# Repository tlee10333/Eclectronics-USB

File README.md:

# Eclectronics Spring 2026 Final Project - Wireless USB Communication Board 
## By: Allan Huang, Trinity Lee, Venkadesh Eswaranandam

This repository contains documentation for a wireless USB communication board. 
TBD

# Documentation
Below are links to documentation provided by the official manufacturers and were used as reference for this project in schematic design and layout. 

## Nordic Semiconductor nRF5340 
[General Documentation Website](https://docs.nordicsemi.com/category/nrf5340-category)

[Download link to Product Specification PDF/Datasheet v1.6](https://docs-be.nordicsemi.com/bundle/ps_nrf5340/page/nRF5340_PS_v1.6.pdf?_LANG=enus) 

## Nordic Semiconductor nRF7002 
[General Documentation Website](https://docs.nordicsemi.com/category/nrf7002-category)

[Download link to Product Specification PDF/Datasheet v1.2](https://docs-be.nordicsemi.com/bundle/ps_nrf7002/attach/nRF7002_PS_v1.2.pdf?_LANG=enus)

## TS3USB30E Mux

[General Documentation Website](https://www.ti.com/product/TS3USB30E?utm_source=google&utm_medium=cpc&utm_campaign=asc-null-null-GPN_EN-cpc-pf-google-ww_en_cons&utm_content=TS3USB30E&ds_k=TS3USB30E&DCM=yes&gclsrc=aw.ds&gad_source=1&gad_campaignid=14388345080&gbraid=0AAAAAC068F08dQr31V7reTsWFYpttdheS&gclid=Cj0KCQjwqPLOBhCiARIsAKRMPZrFZs5P4qY13GjpmxYn9nQQtVWeXslW-kTBu4hEDNIcvVn2RVSppWgaAsXEEALw_wcB)

[Link to Product Specification PDF/Datasheet](https://www.ti.com/lit/ds/symlink/ts3usb30e.pdf?ts=1776081731034&ref_url=https%253A%252F%252Fwww.ti.com%252Fproduct%252FTS3USB30E)

## TBD
[General Documentation Website]()

[Download link to Product Specification PDF/Datasheet]()

# References
Below are links that were used for references (cthis section can be deleted if we want to)

[nRF7002 DK datasheet](https://docs-be.nordicsemi.com/bundle/ug_nrf7002_dk/attach/nRF7002_DK_User_Guide_v1.0.0.pdf?_LANG=enus)

[nRF5340 DK datasheet](https://docs-be.nordicsemi.com/bundle/ug_nrf5340_dk/attach/nRF5340_DK_User_Guide_v2.0.2.pdf?_LANG=enus)

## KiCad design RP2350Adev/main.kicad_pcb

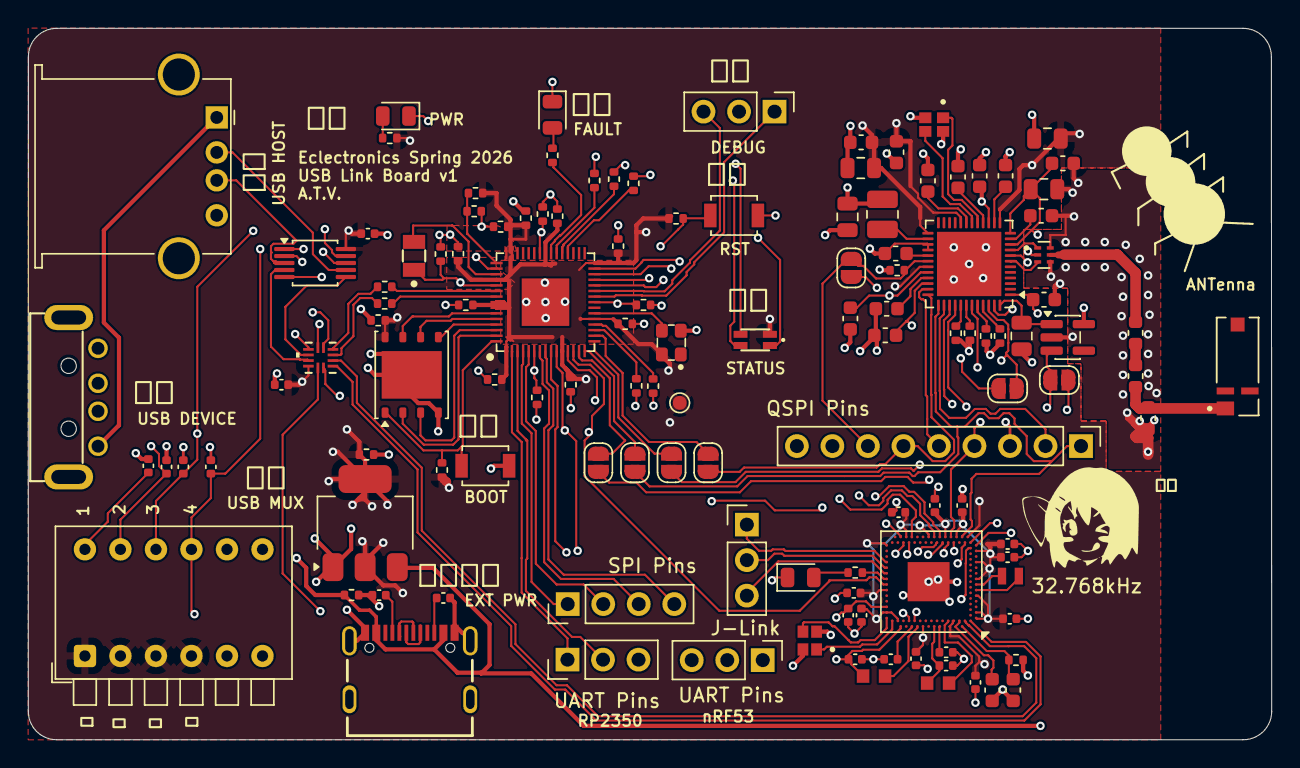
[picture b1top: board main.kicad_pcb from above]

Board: 4 copper layers, 88.9 x 50.9 mm, 124 parts (0 on the bottom side), 111 nets.

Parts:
A301: NN03-320; XCVR_NN03-320
C201, C202: 4.7µF; C_0603_1608Metric
C203, C206, C207, C208, C209: 1.0µF; C_0402_1005Metric
C204, C210, C211, C212, C213, C214, C215, C216, C217: 100nF; C_0402_1005Metric
C205: 2.2nF; C_0402_1005Metric
C301, C314: 0.47uF; C_0603_1608Metric
C302, C303: 100nF; C_0603_1608Metric
C304, C305, C315, C316: 4.7uF; C_0805_2012Metric
C306: 2.2uF; C_0805_2012Metric
C307: 22nF; C_0603_1608Metric
C308: 0.22uF; C_0603_1608Metric
C309, C318: 2.2uF; C_0603_1608Metric
C310, C311, C312, C313: 1uF; C_0603_1608Metric
C317: 10nF; C_0603_1608Metric
C401, C403: 10µF; R_0402_1005Metric
C402, C406, C407, C408, C409, C410, C411, C412, C415, C417: 0.1µF; R_0402_1005Metric
C404, C405, C413, C414, C416: 4.7µF; R_0402_1005Metric
C701, C702: 1uF; C_0402_1005Metric
D201, D402: LED; LED_0805_2012Metric
D401: PWR; LED_0805_2012Metric
D403: IN-S85TATRGB
J201: J-Link; PinHeader_1x03_P2.54mm_Vertical
J202: SPI Pins; PinHeader_1x04_P2.54mm_Vertical
J203: QSPI Pins; PinHeader_1x09_P2.54mm_Vertical
J204: UART Pins; PinHeader_1x03_P2.54mm_Vertical
J401: UART; PinHeader_1x03_P2.54mm_Vertical
J402: DEBUG; PinHeader_1x03_P2.54mm_Vertical
J701: USB_A_Male; USB_A_0480370001
J702: USB_A_Female; USB_A_Stewart_SS-52100-001_Horizontal
J703: USB4105-GF-A
JP101, JP102, JP103, JP104, JP105, JP106, JP107: SolderJumper_2_Open; SolderJumper-2_P1.3mm_Open_RoundedPad1.0x1.5mm
L201: 10uH; INDC1608X95N
L202: 10µH; INDC1608X95N
L301: 7.5nH; L_0603_1608Metric
L302, L303: 2.7nH; L_0603_1608Metric
L304: 3.3uH; L_1008_2520Metric
L401: 3.3µH; AOTA-B201610S3R3-101-T
M701: TS3USB3031RMGR; RMG12_TEX
R101, R102, R404, R405: 27Ω; R_0402_1005Metric
R201: 2.2 Ω; R_0402_1005Metric
R202, R403, R407, R409, R410: 1K; R_0402_1005Metric
R301, R302, R303, R304, R305: 100k; R_0402_1005Metric
R401, R402, R408: 5.1K; R_0402_1005Metric
R406: 33Ω; R_0402_1005Metric
R701, R702, R703, R704: 10K; C_0402_1005Metric
R705, R706: 5.1K; C_0402_1005Metric
S401: RST; SW_SPST_B3U-1000P
S402: BOOT; SW_SPST_B3U-1000P
SW701: SW_DIP_x06; SW_DIP_SPSTx06_Piano_10.8x16.8mm_W7.62mm_P2.54mm
TP101: TestPoint; TestPoint_Pad_D1.0mm
U201: nRF5340-QKxx; Nordic_AQFN-94-1EP_7x7mm_P0.4mm
U301: TCK106AF; SC-74A-5_1.55x2.9mm_P0.95mm
U302: LFD_Diplexer; FIL_LFD182G45DCJD247
U303: nRF7002-QFAA; QFN-48-1EP_6x6mm_P0.4mm_EP4.6x4.6mm
U401: LD1117S33TR_SOT223; SOT-223-3_TabPin2
U402: W25Q32JV; WSON-8-1EP_6x5mm_P1.27mm_EP3.4x4.3mm
U403: RP2350A; RP2350A_QFN-60_EP_7.75x7.75_Pitch0.4mm
U701: TS3USB30EDGSR; VSSOP-10_3x3mm_P0.5mm
X201: 32MHz; XTAL_ABM11W-32.0000MHZ-8-D1X-T3
X202: 32.768kHz; XTAL_CM9V-T1A-32.768KHZ-9PF-20PPM-TA-QC
X301: XTAL-40; XTAL_ABM11W-32.0000MHZ-8-D1X-T3
X401: IQXO-791

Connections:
+1V1: C405.2, C415.2, C416.2, C417.2, L401.1, U403.6 (DVDD), U403.23 (DVDD), U403.39 (DVDD), U403.50 (VREG_FB)
+3V3: C208.2, C209.2, C210.2, C211.2, C212.2, C213.2, C214.2, C215.2, C216.2, C217.2, C305.1, C311.1, C315.1, C318.1, C402.2, C403.1, C404.2, C406.2, C407.2, C408.2, C409.2, C410.2, C411.2, C412.2, C413.2, C701.2, C702.2, D403.3, M701.12 (VCC), R401.1, R402.1, R403.1, R406.2, SW701.1, SW701.2, SW701.3, SW701.4, TP101.1, U201.A19 (VDD), U201.AC1 (VDD), U201.AG1 (VDD), U201.AJ31 (VDD), U201.AL3 (VDD), U201.AL7 (VDD), U201.AL11 (VDD), U201.AL17 (VDD), U201.AL25 (VDD), U201.B8 (VDD), U201.B28 (VDD), U201.C1 (VDD), U201.E1 (VDDH), U201.E31 (VDD), U201.L1 (VDD), U201.N31 (VDD), U201.U1 (VDD), U301.5 (VIN), U303.13 (VBAT), U303.20 (AFEVBAT), U303.25 (BUCKVBAT), U303.31 (BUCKVBATS), U401.2 (VO), U402.8 (VDD), U403.1 (IOVDD), U403.11 (IOVDD), U403.20 (IOVDD), U403.30 (IOVDD), U403.38 (IOVDD), U403.44 (ADC_AVDD), U403.45 (IOVDD), U403.49 (VREG_VIN), U403.53 (USB_OTP_VDD), U403.54 (QSPI_IOVDD), U701.10 (VCC), X401.4 (VS)
+5V: C401.2, J701.1 (VBUS), J702.1 (VBUS), J703.A4B9 (VBUS), J703.B4A9 (VBUS), R201.1, U401.3 (VI)
/RP2350Adev/BOOT: R402.2, S402.2, U402.1 (~CS), U403.60 (~QSPI_CS)
/RP2350Adev/BUCK_EN: JP101.1 (A), U403.28 (GPIO17)
/RP2350Adev/D1+: M701.5 (USB2+), R405.1
/RP2350Adev/D1-: M701.6 (USB2-), R404.1
/RP2350Adev/D2+: R101.2, U403.18 (GPIO14)
/RP2350Adev/D2-: R102.2, U403.19 (GPIO15)
/RP2350Adev/GPIO22: R407.1, U403.34 (GPIO22)
/RP2350Adev/GPIO23: R408.1, U403.35 (GPIO23)
/RP2350Adev/GPIO24: R409.1, U403.36 (GPIO24)
/RP2350Adev/GPIO25: R410.1, U403.37 (GPIO25)
/RP2350Adev/HOST_IRQ: JP102.1 (A), U403.27 (GPIO16)
/RP2350Adev/IOVDD_EN: JP107.2 (B), U403.29 (GPIO18)
/RP2350Adev/MUX1_S0: M701.1 (SEL0), R701.1, SW701.12, U201.R31 (P1.10), U403.13 (GPIO9)
/RP2350Adev/MUX1_S1: M701.2 (SEL1), R702.1, SW701.11, U201.AK26 (P1.09), U403.12 (GPIO8)
/RP2350Adev/MUX2_OE: R703.1, SW701.10, U201.AL23 (P1.08), U403.10 (GPIO7), U701.9 (~OE)
/RP2350Adev/MUX2_S: R704.1, SW701.9, U201.AK24 (P1.07), U403.9 (GPIO6), U701.1 (S)
/RP2350Adev/RUN: R401.2, S401.2, U403.26 (RUN)
/RP2350Adev/SPI_CLK: J202.1, U201.AH2 (SCK/TRACEDATA3/P0.08), U403.4 (GPIO2)
/RP2350Adev/SPI_CLK2: JP106.1 (A), U403.14 (GPIO10)
/RP2350Adev/SPI_MISO: J202.3, U201.AK2 (MISO/TRACEDATA1/P0.10), U403.7 (GPIO4)
/RP2350Adev/SPI_MISO2: JP104.1 (A), U403.16 (GPIO12)
/RP2350Adev/SPI_MOSI: J202.2, U201.AJ1 (MOSI/TRACEDATA2/P0.09), U403.5 (GPIO3)
/RP2350Adev/SPI_MOSI2: JP103.1 (A), U403.15 (GPIO11)
/RP2350Adev/SPI_SS: J202.4, U201.AK4 (CSN/TRACEDATA0/P0.11), U403.8 (GPIO5)
/RP2350Adev/SPI_SS2: JP105.1 (A), U403.17 (GPIO13)
/RP2350Adev/SWCLK: J402.1, U403.24 (SWCLK)
/RP2350Adev/SWDIO: J402.3, U403.25 (SWDIO)
/USB_Mux_Periph/D1+: M701.3 (USB1+), U201.B2 (D+)
/USB_Mux_Periph/D1-: M701.4 (USB1-), U201.B4 (D-)
/USB_Mux_Periph/D3+: M701.7 (MHL+), R101.1
/USB_Mux_Periph/D3-: M701.8 (MHL-), R102.1
/nRF5340/BUCKEN: J203.7, JP101.2 (B), R301.1, U201.AL13 (P0.19), U303.30 (BUCKEN)
/nRF5340/COEX: J203.8, U303.43 (COEX_GRANT)
/nRF5340/HOST_IRQ: J203.9, JP102.2 (B), U201.AL15 (P0.21), U303.46 (HOST_IRQ)
/nRF5340/IOVDD_EN: JP107.1 (A), U201.AL27 (P0.24), U301.3 (CTRL)
/nRF5340/QSPI0: J203.1, JP103.2 (B), U201.AL5 (IO0/P0.13), U303.37 (QSPI_DATA0)
/nRF5340/QSPI1: J203.2, JP104.2 (B), U201.AK8 (IO1/P0.14), U303.38 (QSPI_DATA1)
/nRF5340/QSPI2: J203.3, U201.AK10 (IO2/P0.15), U303.39 (QSPI_DATA2)
/nRF5340/QSPI3: J203.4, U201.AL9 (IO3/P0.16), U303.40 (QSPI_DATA3)
/nRF5340/QSPI_CLK: J203.5, JP106.2 (B), U201.AK12 (SCK/P0.17), U303.35 (QSPI_CLK)
/nRF5340/QSPI_SS: J203.6, JP105.2 (B), U201.AK14 (CSN/P0.18), U303.36 (QSPI_SS)
/nRF5340/RX: J204.2, U201.B24 (P0.30)
/nRF5340/TX: J204.1, U201.B22 (P0.31)
/nRF7002/PWR_IOVDD: C303.1, C312.1, U303.1 (OTPVDD), U303.34 (PWRIOVDD)
/nRF7002/VDD_BUCK: C308.1, C314.1, C316.1, L304.2, U303.15 (RFBUCKVDD), U303.32 (PWRBUCKVDD)
GND: C201.2, C202.2, C203.2, C204.2, C205.2, C206.2, C207.2, C208.1, C209.1, C210.1, C211.1, C212.1, C213.1, C214.1, C215.1, C216.1, C217.1, C301.2, C302.2, C303.2, C304.2, C305.2, C306.2, C307.2, C308.2, C309.2, C310.2, C311.2, C312.2, C313.2, C314.2, C315.2, C316.2, C317.2, C318.2, C401.1, C402.1, C403.2, C404.1, C405.1, C406.1, C407.1, C408.1, C409.1, C410.1, C411.1, C412.1, C413.1, C414.1, C415.1, C416.1, C417.1, C701.1, C702.1, D201.1 (K), D401.1 (K), D402.1 (K), J204.3, J401.3, J402.2, J701.4 (GND), J701.5 (Shield), J702.4 (GND), J702.5 (Shield), J703.A1B12 (GND), J703.B1A12 (GND), J703.S1 (SHELL), J703.S2 (SHELL), J703.S3 (SHELL), J703.S4 (SHELL), L301.2, M701.9 (GND), R301.2, R302.2, R303.2, R304.2, R305.2, R701.2, R702.2, R703.2, R704.2, R705.2, R706.2, S401.1, S402.1, U201.EP (VSS), U301.2 (GND), U302.2 (GND), U302.5 (GND), U302.7 (GND), U303.27 (BUCKVSS), U303.28 (BUCKVSS), U303.47 (VSS), U303.49 (VSS), U401.1 (GND), U402.4 (GND), U402.9 (EP), U403.47 (VREG_PGND), U403.61 (GND), U701.5 (GND), X201.2 (G), X201.4 (G), X301.2 (G), X301.4 (G), X401.2 (GND)
unnamed: A301.1 (A), L301.1, L302.1
unnamed: D201.2 (A), R202.2
unnamed: D401.2 (A), R403.2
unnamed: D402.2 (A), R410.2
unnamed: D403.1, R407.2
unnamed: D403.2, R408.2
unnamed: D403.4, R409.2
unnamed: J201.1, U201.AC31 (~RESET)
unnamed: J201.2, U201.AA31 (SWDIO)
unnamed: J201.3, U201.W31 (SWDCLK)
unnamed: J401.1, U403.2 (GPIO0)
unnamed: J401.2, U403.3 (GPIO1)
unnamed: J701.3 (D+), U701.2 (D1+)
unnamed: J701.2 (D-), U701.8 (D1-)
unnamed: J702.3 (D+), U701.3 (D2+)
unnamed: J702.2 (D-), U701.7 (D2-)
unnamed: J703.A5 (CC1), R706.1
unnamed: J703.B5 (CC2), R705.1
unnamed: L302.2, L303.1
unnamed: M701.11 (D+), U701.4 (D+)
unnamed: M701.10 (D-), U701.6 (D-)
unnamed: L201.1, U201.A21 (DCC)
unnamed: L202.1, U201.B10 (DCCD)
unnamed: C207.1, U201.A13 (DECA)
unnamed: C206.1, L202.2, U201.A15 (DECD)
unnamed: C204.1, U201.A23 (DECN)
unnamed: C203.1, C205.1, L201.2, U201.A27 (DECR), U201.G31 (DECRF)
unnamed: C202.1, U201.B6 (DECUSB)
unnamed: R202.1, U201.U31 (P0.29)
unnamed: C201.1, R201.2, U201.A5 (VBUS)
unnamed: U201.C31 (XC1), X201.3
unnamed: U201.B30 (XC2), X201.1
unnamed: U201.N1 (XL1/P0.00), X202.1
unnamed: U201.R1 (XL2/P0.01), X202.2
unnamed: C306.1, U301.1 (VOUT), U303.48 (IOVDD)
unnamed: U302.1 (2.4G), U303.9 (TXRF0)
unnamed: U302.3 (5G), U303.7 (TXRF1)
unnamed: L303.2, U302.6 (COM)
unnamed: C310.1, U303.19 (AFELDO)
unnamed: L304.1, U303.26 (BUCKOUT)
unnamed: C317.1, U303.29 (BUCKVMID)
unnamed: R303.1, U303.42 (COEX_REQ)
unnamed: R302.1, U303.41 (COEX_STATUS0)
unnamed: C313.1, U303.33 (DIGVDD)
unnamed: C302.1, C304.1, U303.8 (PAVDD1), U303.10 (PAVDD0), U303.12 (PALDO)
unnamed: C307.1, U303.14 (RFVDD)
unnamed: R304.1, U303.44 (SW_CTRL0)
unnamed: R305.1, U303.45 (SW_CTRL1)
unnamed: C301.1, U303.11 (SXLDO)
unnamed: C309.1, U303.16 (XOLDO)
unnamed: U303.18 (XON), X301.3
unnamed: U303.17 (XOP), X301.1
unnamed: U402.5 (DI/IO0), U403.57 (QSPI_SD0)
unnamed: U402.2 (DO/IO1), U403.59 (QSPI_SD1)
unnamed: U402.6 (SCK), U403.56 (QSPI_SCLK)
unnamed: U402.7 (~HOLD/IO3), U403.55 (QSPI_SD3)
unnamed: U402.3 (~WP/IO2), U403.58 (QSPI_SD2)
unnamed: R405.2, U403.52 (USB_D+)
unnamed: R404.2, U403.51 (USB_D-)
unnamed: C414.2, R406.1, U403.46 (VREG_AVDD)
unnamed: L401.2, U403.48 (VREG_LX)
unnamed: U403.21 (XIN), X401.3 (OUT)

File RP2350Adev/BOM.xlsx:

Id | Designator | Footprint | Quantity | Designation | Supplier and ref
1 | R405,R102,R101,R404 | R_0402_1005Metric | 4 | 27Ω
2 | R702,R701,R703,R704 | C_0402_1005Metric | 4 | 10K
3 | C407,C402,C417,C409,C410,C412,C408,C415,C411,C406 | R_0402_1005Metric | 10 | 0.1µF
4 | C201,C202 | C_0603_1608Metric | 2 | 4.7µF
5 | U201 | Nordic_AQFN-94-1EP_7x7mm_P0.4mm | 1 | nRF5340-QKxx
6 | D402,D201 | LED_0805_2012Metric | 2 | LED
7 | R201 | R_0402_1005Metric | 1 | 2.2 Ω
8 | U401 | SOT-223-3_TabPin2 | 1 | LD1117S33TR_SOT223
9 | C302,C303 | C_0603_1608Metric | 2 | 100nF
10 | C212,C214,C204,C215,C210,C213,C216,C211,C217 | C_0402_1005Metric | 9 | 100nF
11 | C308 | C_0603_1608Metric | 1 | 0.22uF
12 | C208,C203,C206,C207,C209 | C_0402_1005Metric | 5 | 1.0µF
13 | R705,R706 | C_0402_1005Metric | 2 | 5.1K
14 | D401 | LED_0805_2012Metric | 1 | PWR
15 | A301 | XCVR_NN03-320 | 1 | NN03-320
16 | J204 | PinHeader_1x03_P2.54mm_Vertical | 1 | UART Pins
17 | R406 | R_0402_1005Metric | 1 | 33Ω
18 | R401,R402,R408 | R_0402_1005Metric | 3 | 5.1K
19 | R410,R409,R202,R403,R407 | R_0402_1005Metric | 5 | 1K
20 | C314,C301 | C_0603_1608Metric | 2 | 0.47uF
21 | C306 | C_0805_2012Metric | 1 | 2.2uF
22 | R305,R302,R301,R303,R304 | R_0402_1005Metric | 5 | 100k
23 | J201 | PinHeader_1x03_P2.54mm_Vertical | 1 | J-Link
24 | L301 | L_0603_1608Metric | 1 | 7.5nH
25 | TP101 | TestPoint_Pad_D1.0mm | 1 | TestPoint
26 | C401,C403 | R_0402_1005Metric | 2 | 10µF
27 | C304,C316,C305,C315 | C_0805_2012Metric | 4 | 4.7uF
28 | C405,C414,C404,C416,C413 | R_0402_1005Metric | 5 | 4.7µF
29 | C307 | C_0603_1608Metric | 1 | 22nF
30 | C313,C310,C312,C311 | C_0603_1608Metric | 4 | 1uF
31 | X301 | XTAL_ABM11W-32.0000MHZ-8-D1X-T3 | 1 | XTAL-40
32 | C317 | C_0603_1608Metric | 1 | 10nF
33 | S401 | SW_SPST_B3U-1000P | 1 | RST
34 | J402 | PinHeader_1x03_P2.54mm_Vertical | 1 | DEBUG
35 | J203 | PinHeader_1x09_P2.54mm_Vertical | 1 | QSPI Pins
36 | U701 | VSSOP-10_3x3mm_P0.5mm | 1 | TS3USB30EDGSR
37 | L202 | INDC1608X95N | 1 | 10µH
38 | J401 | PinHeader_1x03_P2.54mm_Vertical | 1 | UART
39 | X202 | XTAL_CM9V-T1A-32.768KHZ-9PF-20PPM-TA-QC | 1 | 32.768kHz
40 | C309,C318 | C_0603_1608Metric | 2 | 2.2uF
41 | U301 | SC-74A-5_1.55x2.9mm_P0.95mm | 1 | TCK106AF
42 | L201 | INDC1608X95N | 1 | 10uH
43 | U403 | RP2350A_QFN-60_EP_7.75x7.75_Pitch0.4mm | 1 | RP2350A
44 | J702 | USB_A_Stewart_SS-52100-001_Horizontal | 1 | USB_A_Female
45 | S402 | SW_SPST_B3U-1000P | 1 | BOOT
46 | C702,C701 | C_0402_1005Metric | 2 | 1uF
47 | SW701 | SW_DIP_SPSTx06_Piano_10.8x16.8mm_W7.62mm_P2.54mm | 1 | SW_DIP_x06
48 | L304 | L_1008_2520Metric | 1 | 3.3uH
49 | X401 | IQXO-791 | 1 | IQXO-791
50 | L302,L303 | L_0603_1608Metric | 2 | 2.7nH
51 | U302 | FIL_LFD182G45DCJD247 | 1 | LFD_Diplexer
52 | J202 | PinHeader_1x04_P2.54mm_Vertical | 1 | SPI Pins
53 | U303 | QFN-48-1EP_6x6mm_P0.4mm_EP4.6x4.6mm | 1 | nRF7002-QFAA
54 | M701 | RMG12_TEX | 1 | TS3USB3031RMGR
55 | C205 | C_0402_1005Metric | 1 | 2.2nF
56 | X201 | XTAL_ABM11W-32.0000MHZ-8-D1X-T3 | 1 | 32MHz
57 | U402 | WSON-8-1EP_6x5mm_P1.27mm_EP3.4x4.3mm | 1 | W25Q32JV
58 | J703 | USB4105-GF-A | 1 | USB4105-GF-A
59 | J701 | USB_A_0480370001 | 1 | USB_A_Male
60 | D403 | IN-S85TATRGB | 1 | IN-S85TATRGB
61 | L401 | AOTA-B201610S3R3-101-T | 1 | 3.3µH

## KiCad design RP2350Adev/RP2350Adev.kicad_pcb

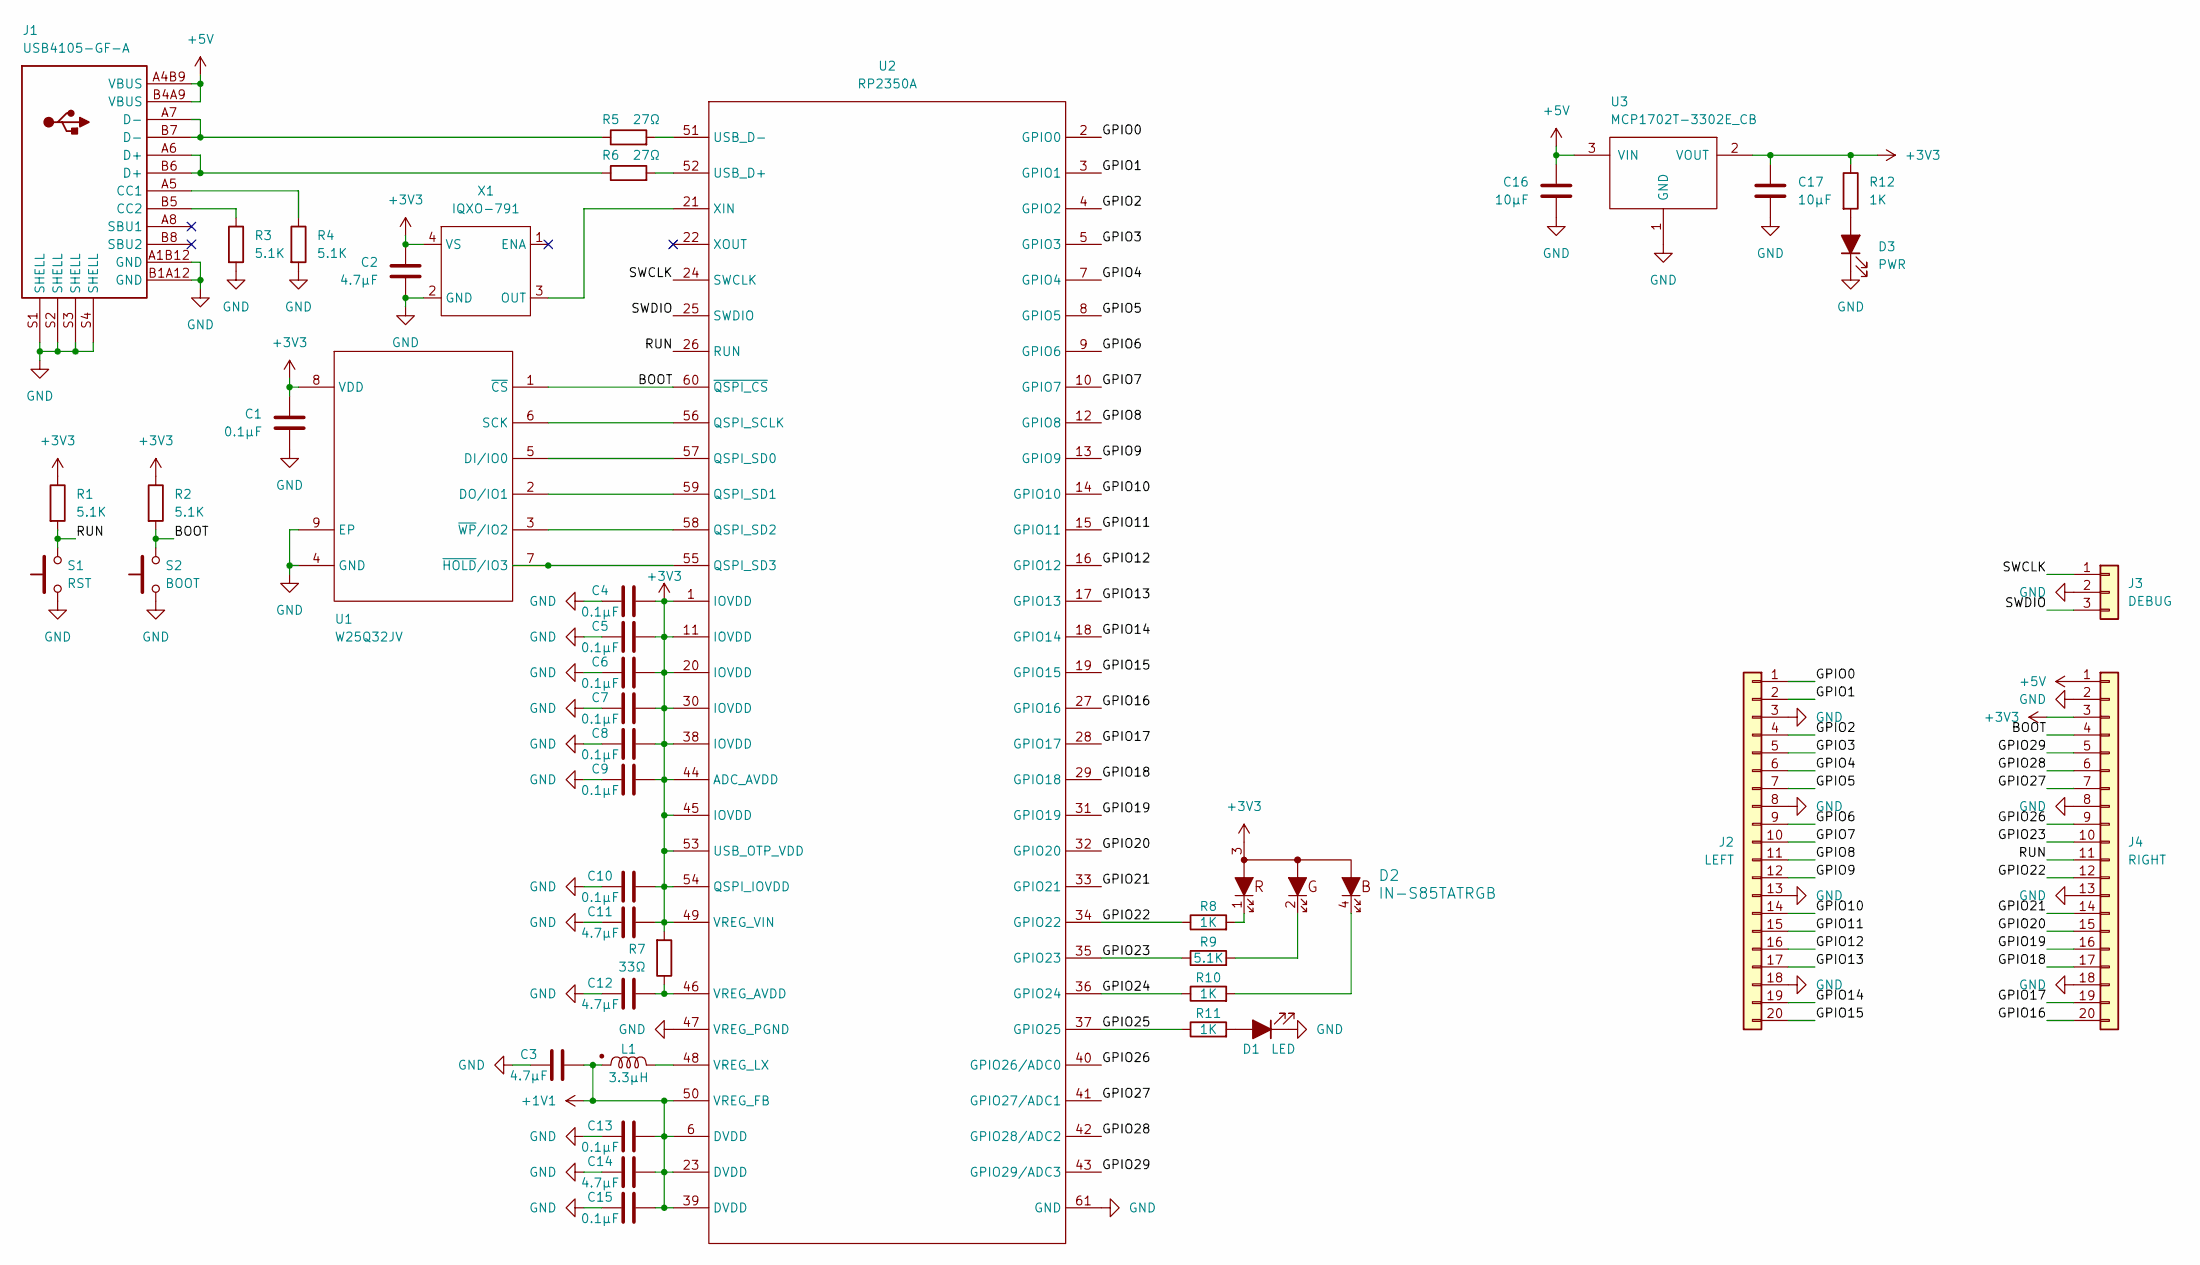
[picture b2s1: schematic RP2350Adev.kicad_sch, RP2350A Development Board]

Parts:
C1, C4, C5, C6, C7, C8, C9, C10, C13, C15: 0.1µF; R_0402_1005Metric
C2, C3, C11, C12, C14: 4.7µF; R_0402_1005Metric
C16, C17: 10µF; R_0402_1005Metric
D1: LED; LED_0805_2012Metric
D2: IN-S85TATRGB
D3: PWR; LED_0805_2012Metric
J1: USB4105-GF-A
J2: LEFT; PinHeader_1x20_P2.54mm_Vertical
J3: DEBUG; PinHeader_1x03_P1.00mm_Vertical
J4: RIGHT; PinHeader_1x20_P2.54mm_Vertical
L1: 3.3µH; AOTA-B201610S3R3-101-T
R1, R2, R3, R4, R9: 5.1K; R_0402_1005Metric
R5, R6: 27Ω; R_0402_1005Metric
R7: 33Ω; R_0402_1005Metric
R8, R10, R11, R12: 1K; R_0402_1005Metric
S1: RST; SW_SPST_B3U-1000P
S2: BOOT; SW_SPST_B3U-1000P
U1: W25Q32JV; WSON-8-1EP_6x5mm_P1.27mm_EP3.4x4.3mm
U2: RP2350A; RP2350A_QFN-60_EP_7.75x7.75_Pitch0.4mm
U3: MCP1702T-3302E_CB; SOT95P255X145-3N
X1: IQXO-791

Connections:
+1V1: C3.2, C13.2, C14.2, C15.2, L1.1, U2.6 (DVDD), U2.23 (DVDD), U2.39 (DVDD), U2.50 (VREG_FB)
+3V3: C1.2, C2.2, C4.2, C5.2, C6.2, C7.2, C8.2, C9.2, C10.2, C11.2, C17.1, D2.3, J4.3, R1.1, R2.1, R7.2, R12.1, U1.8 (VDD), U2.1 (IOVDD), U2.11 (IOVDD), U2.20 (IOVDD), U2.30 (IOVDD), U2.38 (IOVDD), U2.44 (ADC_AVDD), U2.45 (IOVDD), U2.49 (VREG_VIN), U2.53 (USB_OTP_VDD), U2.54 (QSPI_IOVDD), U3.2 (VOUT), X1.4 (VS)
+5V: C16.2, J1.A4B9 (VBUS), J1.B4A9 (VBUS), J4.1, U3.3 (VIN)
/BOOT: J4.4, R2.2, S2.2, U1.1 (~CS), U2.60 (~QSPI_CS)
/GPIO0: J2.1, U2.2 (GPIO0)
/GPIO1: J2.2, U2.3 (GPIO1)
/GPIO2: J2.4, U2.4 (GPIO2)
/GPIO3: J2.5, U2.5 (GPIO3)
/GPIO4: J2.6, U2.7 (GPIO4)
/GPIO5: J2.7, U2.8 (GPIO5)
/GPIO6: J2.9, U2.9 (GPIO6)
/GPIO7: J2.10, U2.10 (GPIO7)
/GPIO8: J2.11, U2.12 (GPIO8)
/GPIO9: J2.12, U2.13 (GPIO9)
/GPIO10: J2.14, U2.14 (GPIO10)
/GPIO11: J2.15, U2.15 (GPIO11)
/GPIO12: J2.16, U2.16 (GPIO12)
/GPIO13: J2.17, U2.17 (GPIO13)
/GPIO14: J2.19, U2.18 (GPIO14)
/GPIO15: J2.20, U2.19 (GPIO15)
/GPIO16: J4.20, U2.27 (GPIO16)
/GPIO17: J4.19, U2.28 (GPIO17)
/GPIO18: J4.17, U2.29 (GPIO18)
/GPIO19: J4.16, U2.31 (GPIO19)
/GPIO20: J4.15, U2.32 (GPIO20)
/GPIO21: J4.14, U2.33 (GPIO21)
/GPIO22: J4.12, R8.1, U2.34 (GPIO22)
/GPIO23: J4.10, R9.1, U2.35 (GPIO23)
/GPIO24: R10.1, U2.36 (GPIO24)
/GPIO25: R11.1, U2.37 (GPIO25)
/GPIO26: J4.9, U2.40 (GPIO26/ADC0)
/GPIO27: J4.7, U2.41 (GPIO27/ADC1)
/GPIO28: J4.6, U2.42 (GPIO28/ADC2)
/GPIO29: J4.5, U2.43 (GPIO29/ADC3)
/RUN: J4.11, R1.2, S1.2, U2.26 (RUN)
/SWCLK: J3.1, U2.24 (SWCLK)
/SWDIO: J3.3, U2.25 (SWDIO)
GND: C1.1, C2.1, C3.1, C4.1, C5.1, C6.1, C7.1, C8.1, C9.1, C10.1, C11.1, C12.1, C13.1, C14.1, C15.1, C16.1, C17.2, D1.1 (K), D3.1 (K), J1.A1B12 (GND), J1.B1A12 (GND), J1.S1 (SHELL), J1.S2 (SHELL), J1.S3 (SHELL), J1.S4 (SHELL), J2.3, J2.8, J2.13, J2.18, J3.2, J4.2, J4.8, J4.13, J4.18, R3.2, R4.2, S1.1, S2.1, U1.4 (GND), U1.9 (EP), U2.47 (VREG_PGND), U2.61 (GND), U3.1 (GND), X1.2 (GND)
unnamed: D1.2 (A), R11.2
unnamed: D2.1, R8.2
unnamed: D2.2, R9.2
unnamed: D2.4, R10.2
unnamed: D3.2 (A), R12.2
unnamed: J1.A5 (CC1), R4.1
unnamed: J1.B5 (CC2), R3.1
unnamed: J1.A6 (D+), J1.B6 (D+), R6.1
unnamed: J1.A7 (D-), J1.B7 (D-), R5.1
unnamed: U1.5 (DI/IO0), U2.57 (QSPI_SD0)
unnamed: U1.2 (DO/IO1), U2.59 (QSPI_SD1)
unnamed: U1.6 (SCK), U2.56 (QSPI_SCLK)
unnamed: U1.7 (~HOLD/IO3), U2.55 (QSPI_SD3)
unnamed: U1.3 (~WP/IO2), U2.58 (QSPI_SD2)
unnamed: R6.2, U2.52 (USB_D+)
unnamed: R5.2, U2.51 (USB_D-)
unnamed: C12.2, R7.1, U2.46 (VREG_AVDD)
unnamed: L1.2, U2.48 (VREG_LX)
unnamed: U2.21 (XIN), X1.3 (OUT)

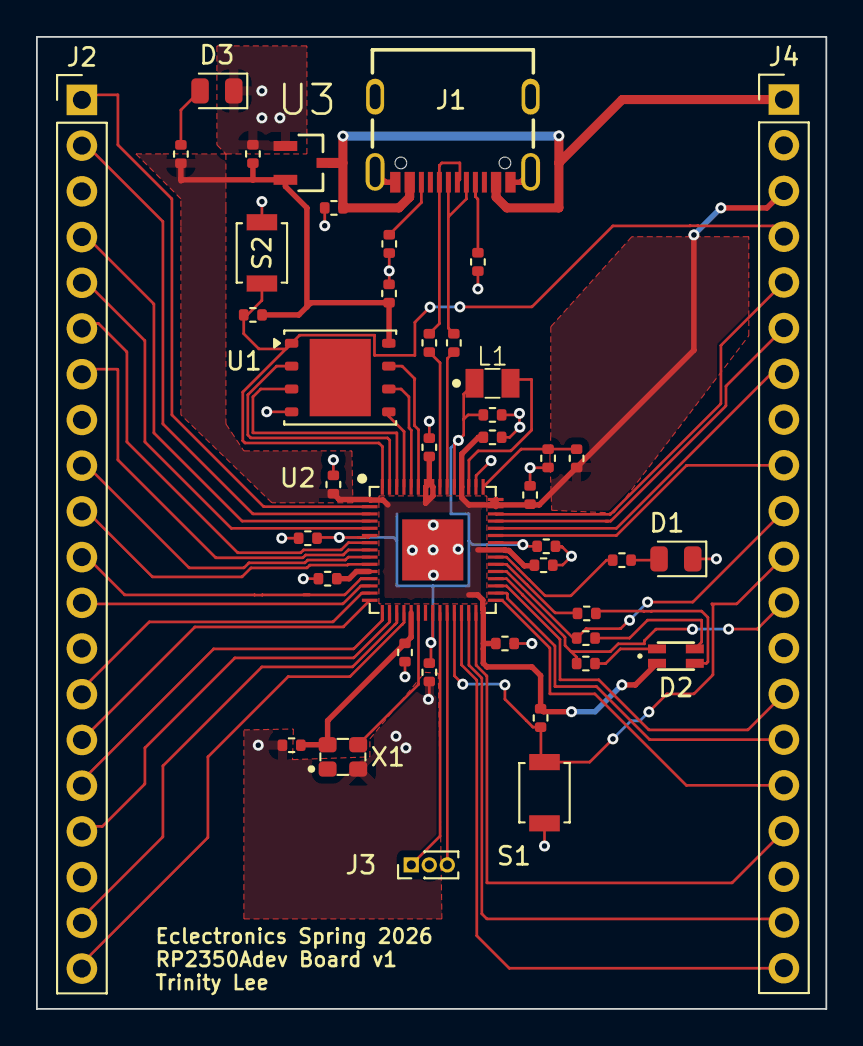
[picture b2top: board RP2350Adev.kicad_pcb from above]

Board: 2 copper layers, 43.9 x 54.0 mm, 43 parts (0 on the bottom side), 57 nets.

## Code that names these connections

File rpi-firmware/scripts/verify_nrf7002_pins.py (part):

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verify_nrf7002_pins.py -- Static DTS pin-trace verification for nRF7002 EK on Pico + FlexyPin.

Traces every logic signal the nRF70 WiFi driver uses through three layers:
  nRF7002 EK connector  ->  Arduino header  ->  FlexyPin (pico_header)  ->  RP2350 gpio0

Also compares the resulting GPIO numbers against the expected values in app.overlay,
and side-by-side against the reference nRF5340 DK + nRF7002 EK setup.
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# nrf7002ek_common.dtsi (zephyrproject workspace)
# Signal -> (arduino_pin_name, flags)
NRF7002_EK_SIGNALS = {
    "BUCKEN":      ("D1",  "GPIO_ACTIVE_HIGH | GPIO_PULL_DOWN"),
    "IOVDD_CTRL":  ("D0",  "GPIO_ACTIVE_HIGH | GPIO_PULL_DOWN"),
    "HOST_IRQ":    ("D7",  "GPIO_ACTIVE_HIGH"),
    # SPI signals come from arduino_spi bus (D10=CS, D11=MOSI, D12=MISO, D13=SCK)
    "SPI_CS":      ("D10", "SPI_BUS"),
    "SPI_MOSI":    ("D11", "SPI_BUS"),
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# rpi_pico_uno_flexypin.overlay (zephyrproject and nrf-sdk both identical)
# gpio-map: <ARDUINO_HEADER_R3_Dxx 0 &pico_header N 0>
# The map key is the ARDUINO numeric index; value is pico_header index.
# pico_header[N] -> gpio0 N  (1:1 in rpi_pico2.dtsi)
FLEXYPIN_MAP = {
    6:  1,   # D0  -> GP1
    7:  0,   # D1  -> GP0
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    21: 21,  # D15 -> GP21
}

# rpi_pico2.dtsi (zephyrproject) -- pico_header[N] maps directly to gpio0 N
# pico_header indices used: 0,1,2,3,4,5,6,7,8,9,16,17,18,19,20,21,22,26,27,28
# All map 1:1 to gpio0 (gpio0 0..28).
def pico_header_to_gpio0(n):
    return n  # 1:1 mapping

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
# app.overlay -- the expected/intended GPIO numbers for &nrf70 and comments
APP_OVERLAY_EXPECTED = {
    "BUCKEN":     0,   # <&gpio0 0 GPIO_ACTIVE_HIGH>
    "IOVDD_CTRL": 1,   # <&gpio0 1 GPIO_ACTIVE_HIGH>
    "HOST_IRQ":   9,   # <&gpio0 9 GPIO_ACTIVE_HIGH>
    "SPI_CS":     17,  # SPI0_CSN (from pinctrl)
    "SPI_MOSI":   19,  # SPI0_TX
    "SPI_MISO":   16,  # SPI0_RX
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# nrf5340dk_common.dtsi -- arduino_header -> nRF5340 GPIO
# gpio-map: <ARDUINO_HEADER_R3_Dxx 0 &gpioN pin 0>
NRF5340_ARDUINO_MAP = {
    6:  ("gpio1", 0),   # D0  -> P1.00
    7:  ("gpio1", 1),   # D1  -> P1.01
    8:  ("gpio1", 4),   # D2  -> P1.04
    9:  ("gpio1", 5),   # D3  -> P1.05
    10: ("gpio1", 6),   # D4  -> P1.06
    11: ("gpio1", 7),   # D5  -> P1.07
    12: ("gpio1", 8),   # D6  -> P1.08
    13: ("gpio1", 9),   # D7  -> P1.09
    14: ("gpio1", 10),  # D8  -> P1.10
    15: ("gpio1", 11),  # D9  -> P1.11
    16: ("gpio1", 12),  # D10 -> P1.12  [SPI4 CS via cs-gpios]
    17: ("gpio1", 13),  # D11 -> P1.13  [SPI4 MOSI]
    18: ("gpio1", 14),  # D12 -> P1.14  [SPI4 MISO]
    19: ("gpio1", 15),  # D13 -> P1.15  [SPI4 SCK]
}

# nRF5340 DK SPI4 pinctrl (nrf5340_cpuapp_common-pinctrl.dtsi)
# SPI4_default:  SPIM_SCK=P1.15, SPIM_MISO=P1.14, SPIM_MOSI=P1.13
# CS is via cs-gpios = <&arduino_header 16 GPIO_ACTIVE_LOW> -> P1.12
NRF5340_SPI4 = {
    "SPI_CS":   ("gpio1", 12),
    "SPI_MOSI": ("gpio1", 13),
    "SPI_MISO": ("gpio1", 14),
    "SPI_CLK":  ("gpio1", 15),
}

# ---------------------------------------------------------------------------
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# ---------------------------------------------------------------------------

def trace_signal_pico(signal):
    """Trace a signal from nRF7002 EK through FlexyPin to RP2350 gpio0."""
    arduino_name, flags = NRF7002_EK_SIGNALS[signal]
    arduino_idx = ARDUINO[arduino_name]

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        "arduino_name": arduino_name,
        "arduino_idx":  arduino_idx,
        "pico_header":  FLEXYPIN_MAP[arduino_idx],
        "gpio0_pin":    gp,
    }


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    # -----------------------------------------------------------------------
    print("Signals tested (coex excluded per spec):")
    print("-" * 72)
    header = f"  {'Signal':<14} {'ArduinoPin':<12} {'PicoHeader':<12} {'gpio0 pin':<10} {'app.overlay':<12} Status"
    print(header)
    print()

    for signal, info in SIGNAL_INFO.items():
        trace = trace_signal_pico(signal)
        expected = APP_OVERLAY_EXPECTED[signal]
        actual   = trace["gpio0_pin"]
        ok = (actual == expected)
        if not ok:
            all_pass = False
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        print(f"               {PASS}  {override_note}")
        print()

    print(f"  HOST_IRQ     nrf7002ek_common.dtsi flags: GPIO_ACTIVE_HIGH")
    print(f"               {PASS}  No pull-down, app.overlay preserves GPIO_ACTIVE_HIGH")
    print()

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    print(f"  Pico (RP2350)  : Hardware CS via PL022 SPI controller on GP17 (SPI0_CSN_P17)")
    print(f"                   No cs-gpios needed -- PL022 native CS is active-LOW by default")
    print(f"  nRF5340 DK     : Software GPIO CS via cs-gpios=<&arduino_header 16 GPIO_ACTIVE_LOW>")
    print(f"                   Maps to P1.12 (gpio1 12)")
    print(f"  {PASS}  Both result in active-LOW CS toggling on Arduino D10 -- functionally equivalent")
    print()

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    print("-" * 72)
    bucken_nrf  = trace_signal_nrf5340("BUCKEN")
    iovdd_nrf   = trace_signal_nrf5340("IOVDD_CTRL")
    print(f"  nRF5340 DK BUCKEN    = {bucken_nrf['label']}  (same pin as UART1_TX)")
    print(f"  nRF5340 DK IOVDD_CTRL= {iovdd_nrf['label']}  (same pin as UART1_RX)")
    print(f"  -> nrf5340dk_nrf5340_cpuapp.overlay disables gpio_fwd to release P1.00/P1.01")
    print()
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    for signal in SIGNAL_INFO:
        p = trace_signal_pico(signal)
        n = trace_signal_nrf5340(signal)
        pico_str = f"GP{p['gpio0_pin']} (gpio0)"
        nrf_str  = f"{n['label']} ({n['gpio_port']})"
        # The *Arduino pin* must match -- the actual MCU GPIO will differ between boards
        pin_match = (p['arduino_name'] == n['arduino_name'])
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
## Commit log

2026-04-02 Defaulit RP board
2026-04-10 add nrf70
2026-04-13 Added nRF5340
2026-04-13 Adding gitignore
2026-04-13 add footprints
2026-04-13 Resetting it
2026-04-13 Muxful beginnings
2026-04-13 Updated nRF5340 work
2026-04-13 Updated ignore file with more
2026-04-13 Redundant Files
2026-04-13 Deleting more Redundant Files
2026-04-13 adding readme file
2026-04-13 fixed readme
2026-04-13 typo
2026-04-13 Updated nRF5340 schematic
2026-04-14 link hierarchical sheet and switch from QSPI to SPI
2026-04-14 Mucful Returns
2026-04-14 add main
2026-04-14 better ignore file
2026-04-15 Updated nRF5340 with footprints and labels
2026-04-15 Muxful Developings
2026-04-15 Muxful Schematics Done (Added external standalone 5V supply USB-C connector)
2026-04-15 Muxful Assignings of Components and Foots
2026-04-15 Added UART and final footprints
2026-04-15 Combine subsheets
2026-04-17 Layout Assembly Attempt (Components not being transferred as expected, major issues)
2026-04-18 Combine subcircuits
2026-04-18 Layout mostly complete, need to finalize layers
2026-04-18 RF layout
2026-04-18 Pushing Added Arts, Fixes to Overlapping Labels
2026-04-18 fix footprint errors
2026-04-19 Add silk
2026-04-21 final fab files
2026-04-21 add rpi pico firmware
2026-04-23 Adding interactive BOM, muxful death
2026-04-30 Debug Version of USB-SPI bridge for RP2350
